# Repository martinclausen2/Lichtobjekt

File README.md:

# Lichtobjekt

The "Lichtobjekt" projects allows to create portable lighting appliances.

## Features

- Two independent LED driver channels
  - Flicker free brightness control through current adjustment
- Integrated Li Ion battery charger
- Status LED to indicate power on, channel, standby, and charging status
- Brightness measurement to adjust brightness at power on
- IR remote control (receiver and sender)
  -	Option to network devices
- Single rotational encoder and switch needed to control
- Embedded terminal to control settings, clock, and alarms

## Technical Features
- ARM Cortex M3 based STM32L151 microcontroller
  - EEPROM for permanent storage of settings
- RC5 based communication (sender and receiver)
- Two TPS61165DBVT step-up LED driver with PWM adjustment of LED driving current up to 350mA
- High dynamic brightness measurement with low cost phototransistor SFH320
- Low power design
  - Shutdown for IR receiver and voltage measurement
  - MCU power down and frequency adjustment
  - Low power logic voltage regulation with MCP1703
- Integrated Li Ion charger based on BQ2057WSN
  - Battery temperature monitoring
  - Charging status
  - 2S cell configuration
- PCB prepared (not used in current software) for 
  - Acceleration sensor MMA8452
  - Pin headers for extension with additional I2C devices, LCD, or LED drivers
  - RTC RV3029-C2 - currently the MCU's internal RTC is utilized 
  - EEPROM from 24CXXX series with I2C connection - currently the MCU's internal EEPROM is utilized, the EEPROM can be populated if other STM32 MCU are to be used which do not contain a EEPROM

# Design description

## Hardware

### MCU
The STM32L1 series features for this application relevant features like a large number of timers, specific low power modes, and an embedded EEPROM.

The MCU can be programmed and debugged via SWD accessable through a custom pin header, that also exposes the serial port.

### LED Driver
To drive a sufficient number of LEDs for edge illumination without efficiency reducing current balancing resistors, a LED driver with a step-up topology was selected. A two cell battery increases the efficiency of the step-up LED driver.

### RC5 receiver and sender

A IR emitting diode is driven by a small MOSFET from the PWM output of a timer in the MCU to send RC5 commands.

To receive RC5 commands the output of the IR receiver is sampled at a rate of about 4.5kHz by the MCU. The power supply of the IR receiver is cut in standby mode to prevent the battery to be drained prematurely.

### Brightness Sensor

The ambient brightness is sensed via an in expensive a broadly available phototransistor SFA 320. To enhance the dynamic range, the MCU can switch the bias current between two different levels.
The precision is fully sufficient to adjust the brightness of the power LEDs at power on and dim the status LED in standby.

### Battery Charger

The battery charger follows example application of the BQ2057 charging controller. The input voltage should be 9 V to avoid excessive power dissipation in the charging current regulating power transistor.
In newer hardware revision could switch off the charger during overvoltage conditions - However, the implementation in software is currently pending.
The status output is read by the MCU, that controls the status LED accordingly.
A temperature sensor is used to stop the charging if an overtemperature condition of the battery is detected.

## Software

TBA

## Known Limitations
- Very low power modes of MCU cannot be used, since to polarity of the encoder switch is not suitable.
- The MCU does not switch the battery charger off, if the input voltage would lead to a thermal overload of the charging transistor.
The batch of pcb made is missing the required hardware prerequisites. The latest version contains the required circuits, but has not been manufactured yet.
The batch is also missing the MOSFET to shutdown the battery temperature and external voltage measurement. Due to the high leakage current of the charging transistor, the battery is drained with about 400µA also during power down.
- The ioc file currently targets the STM32L151 which is not available anymore. The setup can easily be changed to the STM32L151A.

# User Manual

The user interface is rather simplistic.

Turning the encoder increases or decreases the brightness.
The integrated push button is used to select functionality and change between on and off.
Detailed settings can be adjusted via the serial terminal.

Coming from standby a short button press switches the light on. A long button press activates the networked mode, where other compatible lighting appliances receive commands to follow on, off, and brightness settings.

When the appliance in on the short button press selects between the two individual LED strings and a mode where the brightness is modulated between the two channels.

When the button is pressed, the status led previews a for a short time the next selected functionality.

Standby can be reached via a long button pressed from power on mode.

| LED Color 	| Condition | Status   | 
| :------------ | :------ | :------- |
| red			|         | standby  |
| white			|         | power on |
| blue flashing |         | charging |
| green flash	| while adjusting brightness | maximum brightness reached |
| red flash		| while adjusting brightness | minimum brightness reached |
| white flash	| pressing the button short | selected first LED channel  |
| red flash		| pressing the button short | selected second LED channel |
| pink flash	| pressing the button short | selected mood light mode	      |
| blue flash	| pressing the button long to power off | duration of flash corresponds to the charging status of the battery |
| green flash	| pressing the button very long | cancel button pressed |

The white flash is actually not visible, since the LED is already shining white.

# Configuration Manual

The serial port uses the following parameter 115200 Baud rate, data site 8, parity none, stop bits 1

The commands can be listed by sending the command 'help'.

## Available Commands

### Set Brightness

	bright [type] <-c channel_no> <-b brightness_value>

set brightness values

| Type | Decription |
| :--- | :--------- |
| 0 | Brightness last used before lights were switched off. |
| 1 | Minimum brightness when switched on |
| 2 | Maximum brightness any time |
| 3 | Maximum brightness when an alarm is triggered |
| 4 | PWM offset for brightness |
| 5 | Current brightness |

### Get External Brightness

	getextbright

Get the external brightness from the phototransistor

### Infrared Remote Control

	remote <-a address> <-rm receiver mode> <-sm sender mode> <-sa send address> <-sd send data>

set infrared remote parameters

| Mode | Decription |
| :--- | :--------- |
| 0 | Off |
| 1 | Alarm |
| 2 | Condional |
| 3 | All |

### Set Date and Time

	time [hour] [minute] [second]

set time of RTC

	date [2 digit year] [month] [day] [w] with w weekday

set date of RTC

	timestamp

get date and time from RTC

### Alarm

	alarmschedule [alarm no] <-w weekday> <-h hour> <-m minute>

set alarm schedule

	alarmsetting <-f time to fade-in light>

set alarm parameters
	
	alarm <-a 1 | 0> <-s alarm skip count>

trigger, reset, set alarm skip count

### Power and Battery

	power <-l 1 | 0>\r\n<-ub battery voltage> <-mub minimum battery voltage>\r\n<-up external power voltage> <-mup minimum external power voltage difference>

switch light, set min external power and battery voltage and calibration

Voltages are given in mV.

### Reset Settings

	reset

reset settings to factory defaults

### Status LED

	statusled [flash count]

flash status led

### Mood light

	fadelight <-f 1 | 0> time - <-t time> <-b brightness> <-mb maximum brightness>

switch and parameterize on mood light

### Version

	version

show STM32 software version

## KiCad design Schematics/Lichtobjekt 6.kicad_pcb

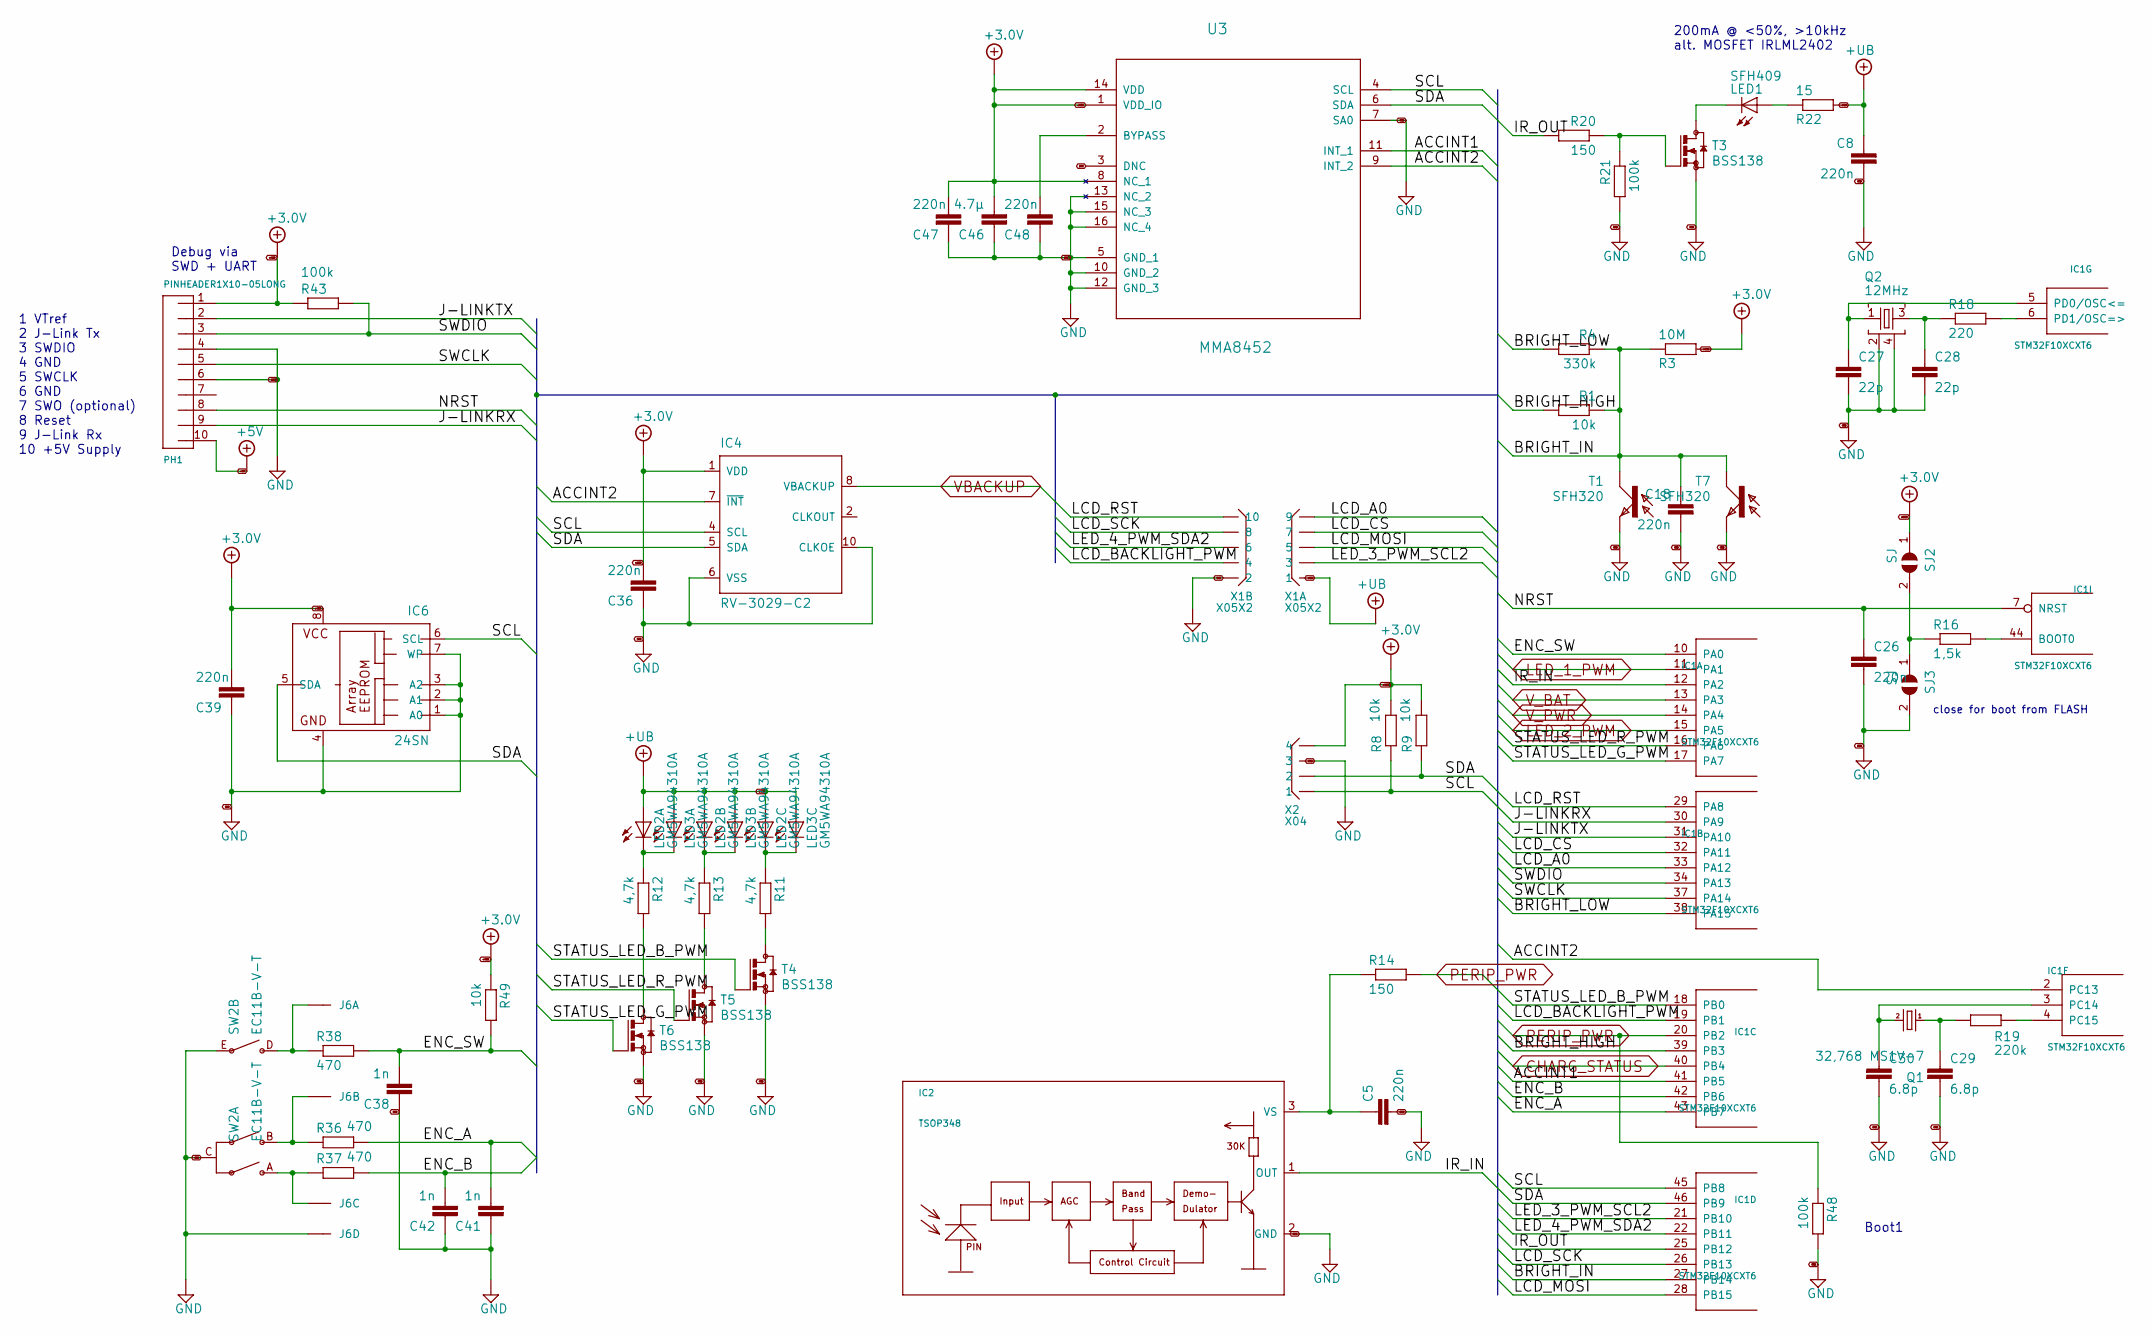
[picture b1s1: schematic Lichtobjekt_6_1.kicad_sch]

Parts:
C5, C8, C18, C26, C36, C39, C47, C48: 220n; C0603
C27, C28: 22p; C0603
C29, C30: 6.8p; C0603
C38, C41, C42: 1n; C0603
C46: 4.7µ; C0805
IC1: STM32F10XCXT6; TQFP48
IC2: TSOP348
IC4: RV-3029-C2; SON-10
IC6: 24SN; SO-08
J6: 22-?-0427-2041; 6410-04
LED1: SFH409; LED3MM
LED2, LED3: GM5WA94310A
PH1: PINHEADER1X10-05LONG; PINHEADER_005-1-10
Q1: 32,768 MS1V-7; MS1V-T1K
Q2: 12MHz; 3.4X2.7-4-PAD
R1, R8, R9, R49: 10k; R0805
R3: 10M; R0805
R4: 330k; R0805
R11, R12, R13: 4,7k; R0805
R14, R20: 150; R0805
R16: 1,5k; R0805
R18: 220; R0805
R19: 220k; R0805
R21, R43, R48: 100k; R0805
R22: 15; R1206
R36, R37, R38: 470; R0805
SJ2, SJ3: SJ
SW2: EC11B-V-T; EC11B-V
T1, T7: SFH320; LED_PLCC-2
T3, T4, T5, T6: BSS138; SOT23
U3: MMA8452; LGA16R50P3X5_300X300X100
X1: X05X2; X10N-IDC
X2: X04; X04N-SIL

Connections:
+5V: PH1.10; also elsewhere on the board
+UB: C8.1, LED2.1 (A), LED2.2 (A), LED2.3 (A), LED3.1 (A), LED3.2 (A), LED3.3 (A), R22.2, X1.1; also elsewhere on the board
+UB3: C36.1, C39.1, C46.2, C47.1, IC4.1 (VDD), IC6.8 (VCC), PH1.1, R3.2, R8.2, R9.2, R43.1, R49.1, SJ2.1, U3.1 (VDD_IO), U3.8 (NC_1), U3.14 (VDD), X2.4; also elsewhere on the board
/Lichtobjekt 6_1/ACCINT1: IC1.41 (PB5), U3.11 (INT_1)
/Lichtobjekt 6_1/ACCINT2: IC1.2 (PC13), IC4.7 (~INT), U3.9 (INT_2)
/Lichtobjekt 6_1/BRIGHT_HIGH: IC1.39 (PB3), R1.2
/Lichtobjekt 6_1/BRIGHT_IN: C18.1, IC1.27 (PB14), R1.1, R3.1, R4.1, T1.1 (C), T7.1 (C)
/Lichtobjekt 6_1/BRIGHT_LOW: IC1.38 (PA15), R4.2
/Lichtobjekt 6_1/ENC_A: C41.2, IC1.43 (PB7), R36.2
/Lichtobjekt 6_1/ENC_B: C42.2, IC1.42 (PB6), R37.2
/Lichtobjekt 6_1/ENC_SW: C38.2, IC1.10 (PA0), R38.2, R49.2
/Lichtobjekt 6_1/IR_IN: IC1.12 (PA2), IC2.1 (OUT)
/Lichtobjekt 6_1/IR_OUT: IC1.25 (PB12), R20.2
/Lichtobjekt 6_1/J-LINKRX: IC1.30 (PA9), PH1.9
/Lichtobjekt 6_1/J-LINKTX: IC1.31 (PA10), PH1.2
/Lichtobjekt 6_1/LCD_A0: IC1.33 (PA12), X1.9
/Lichtobjekt 6_1/LCD_BACKLIGHT_PWM: IC1.19 (PB1), X1.4
/Lichtobjekt 6_1/LCD_CS: IC1.32 (PA11), X1.7
/Lichtobjekt 6_1/LCD_MOSI: IC1.28 (PB15), X1.5
/Lichtobjekt 6_1/LCD_RST: IC1.29 (PA8), X1.10
/Lichtobjekt 6_1/LCD_SCK: IC1.26 (PB13), X1.8
/Lichtobjekt 6_1/LED_3_PWM_SCL2: IC1.21 (PB10), X1.3
/Lichtobjekt 6_1/LED_4_PWM_SDA2: IC1.22 (PB11), X1.6
/Lichtobjekt 6_1/NRST: C26.1, IC1.7 (NRST), PH1.8
/Lichtobjekt 6_1/SCL: IC1.45 (PB8), IC4.4 (SCL), IC6.6 (SCL), R8.1, U3.4 (SCL), X2.1
/Lichtobjekt 6_1/SDA: IC1.46 (PB9), IC4.5 (SDA), IC6.5 (SDA), R9.1, U3.6 (SDA), X2.2
/Lichtobjekt 6_1/STATUS_LED_B_PWM: IC1.18 (PB0), T4.1 (G)
/Lichtobjekt 6_1/STATUS_LED_G_PWM: IC1.17 (PA7), T6.1 (G)
/Lichtobjekt 6_1/STATUS_LED_R_PWM: IC1.16 (PA6), T5.1 (G)
/Lichtobjekt 6_1/SWCLK: IC1.37 (PA14), PH1.5
/Lichtobjekt 6_1/SWDIO: IC1.34 (PA13), PH1.3, R43.2
CHARG_STATUS: IC1.40 (PB4); also elsewhere on the board
DNC: U3.3 (DNC)
GND: C5.2, C8.2, C18.2, C26.2, C27.2, C28.2, C29.2, C30.2, C36.2, C38.1, C39.2, C41.1, C42.1, C46.1, C47.2, C48.2, IC2.2 (GND), IC4.6 (VSS), IC4.10 (CLKOE), IC6.1 (A0), IC6.2 (A1), IC6.3 (A2), IC6.4 (GND), IC6.7 (WP), J6.4, PH1.4, PH1.6, Q2.2, Q2.4, R21.2, R48.2, SJ3.2, SW2.C, SW2.E, T1.2 (E), T3.2 (S), T4.2 (S), T5.2 (S), T6.2 (S), T7.2 (E), U3.5 (GND_1), U3.7 (SA0), U3.10 (GND_2), U3.12 (GND_3), U3.13 (NC_2), U3.15 (NC_3), U3.16 (NC_4), X1.2, X2.3; also elsewhere on the board
LED_1_PWM: IC1.11 (PA1); also elsewhere on the board
LED_2_PWM: IC1.15 (PA5); also elsewhere on the board
unnamed: C5.1, IC2.3 (VS), R14.1
unnamed: C27.1, IC1.5 (PD0/OSC<=), Q2.1
unnamed: C28.1, Q2.3, R18.1
unnamed: C29.1, Q1.1, R19.1
unnamed: C30.1, IC1.3 (PC14), Q1.4 (2)
unnamed: C48.1, U3.2 (BYPASS)
unnamed: IC1.4 (PC15), R19.2
unnamed: IC1.6 (PD1/OSC=>), R18.2
unnamed: IC1.44 (BOOT0), R16.2
unnamed: J6.1, R38.1, SW2.D
unnamed: J6.2, R36.1, SW2.B
unnamed: J6.3, R37.1, SW2.A
unnamed: LED1.A, R22.1
unnamed: LED1.K (C), T3.3 (D)
unnamed: LED2.4 (C), LED3.4 (C), R13.1
unnamed: LED2.5 (C), LED3.5 (C), R12.1
unnamed: LED2.6 (C), LED3.6 (C), R11.1
unnamed: R11.2, T4.3 (D)
unnamed: R12.2, T6.3 (D)
unnamed: R13.2, T5.3 (D)
unnamed: R16.1, SJ2.2, SJ3.1
unnamed: R20.1, R21.1, T3.1 (G)
PERIP_PWR: IC1.20 (PB2), R14.2, R48.1; also elsewhere on the board
VBACKUP: IC4.8 (VBACKUP); also elsewhere on the board
V_BAT: IC1.13 (PA3); also elsewhere on the board

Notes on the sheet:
Debug via SWD + UART
200mA @ <50%, >10kHz alt. MOSFET IRLML2402
close for boot from FLASH
Boot1
1 VTref 2 J-Link Tx 3 SWDIO 4 GND 5 SWCLK 6 GND 7 SWO (optional) 8 Reset 9 J-Link Rx 10 +5V Supply

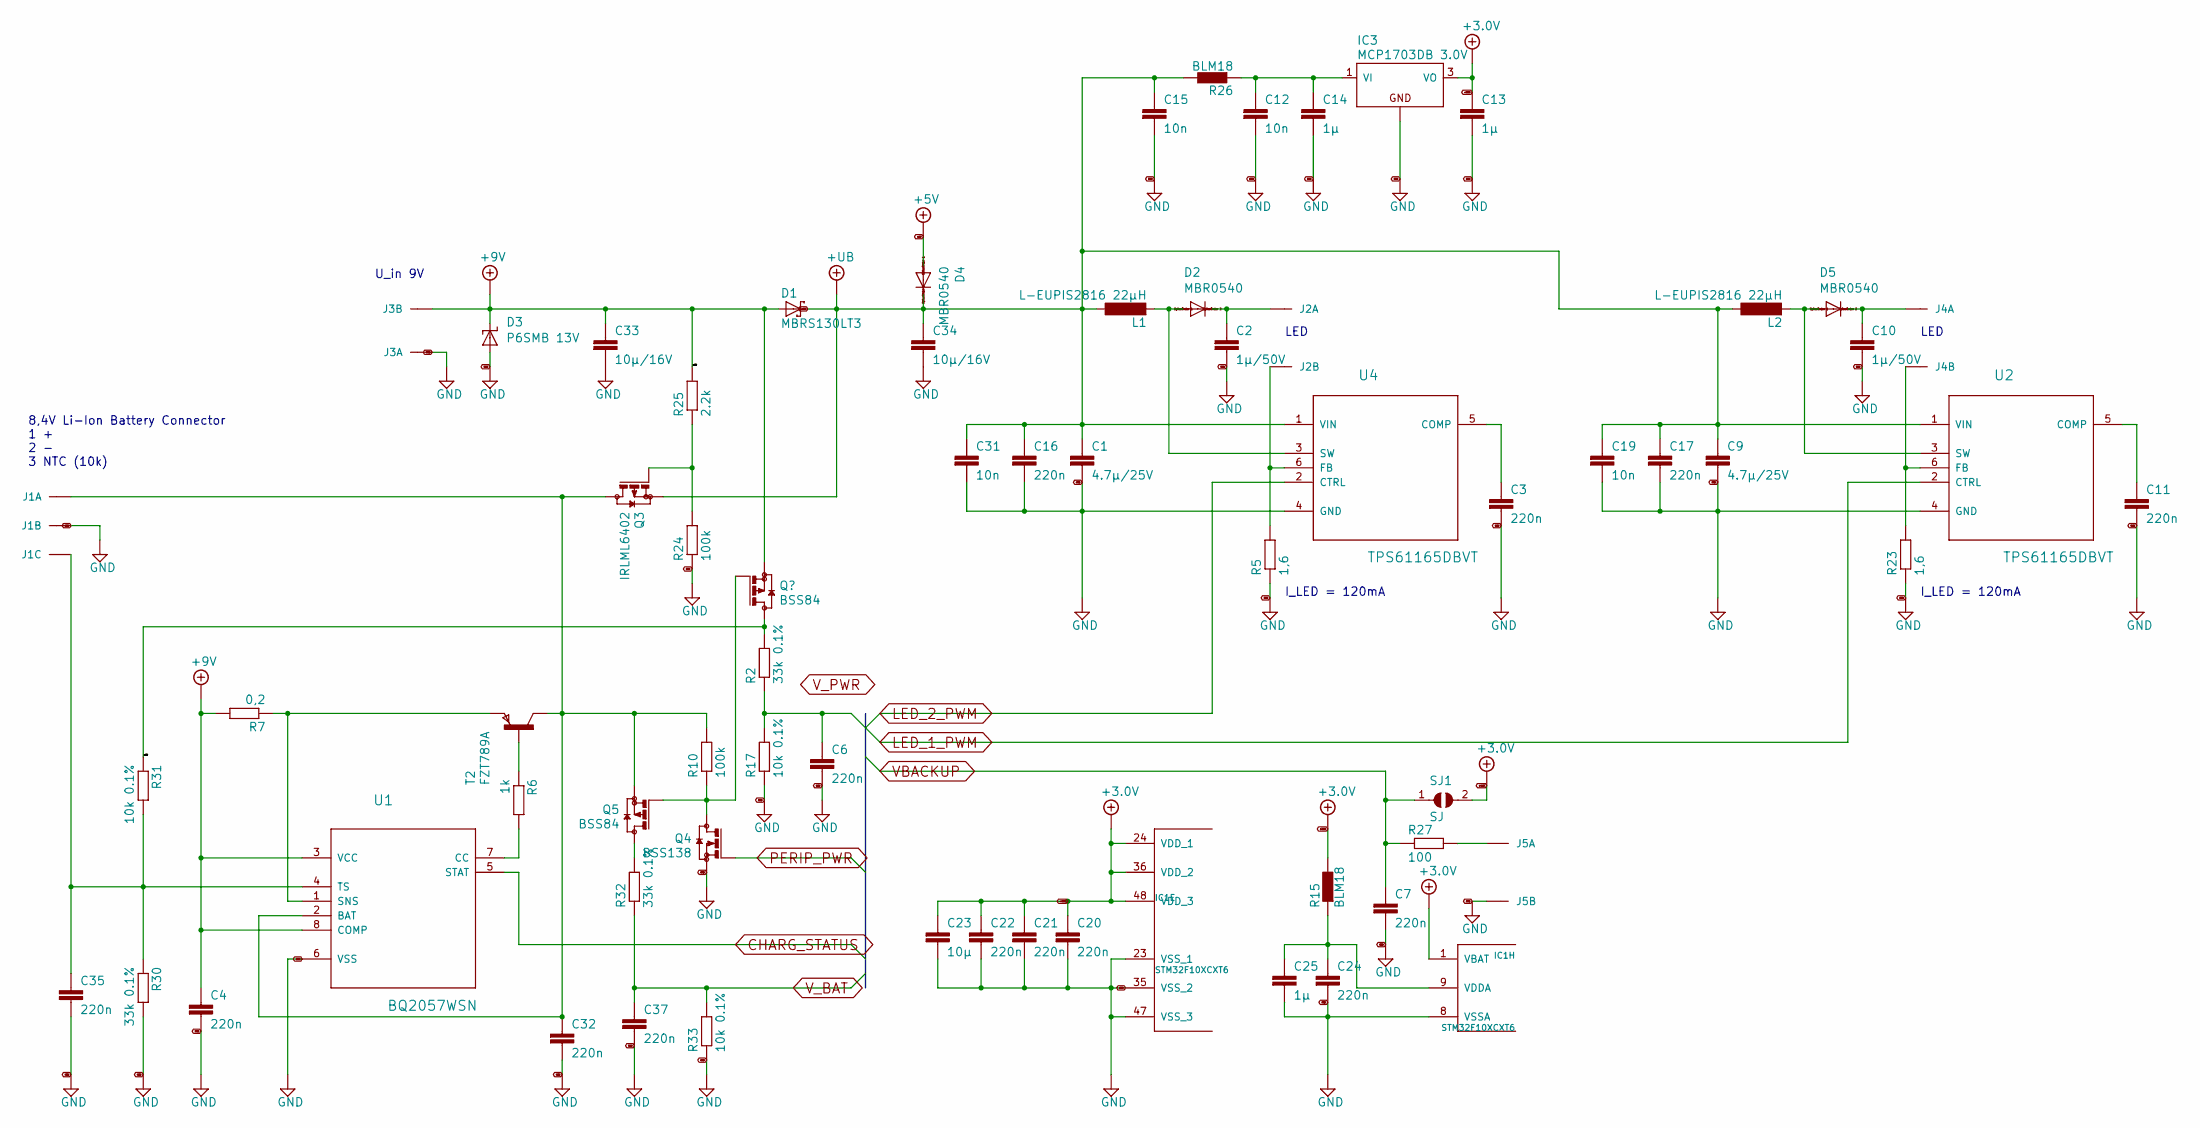
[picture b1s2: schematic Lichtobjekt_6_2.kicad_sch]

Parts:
C1, C9: 4.7µ/25V; C0805
C2, C10: 1µ/50V; C0805
C3, C4, C6, C7, C11, C16, C17, C20, C21, C22, C24, C32, C35, C37: 220n; C0603
C12, C15, C19, C31: 10n; C0603
C13, C14, C25: 1µ; C0805
C23: 10µ; C0805
C33, C34: 10µ/16V; C1210
D1: MBRS130LT3; SMB
D2, D4, D5: MBR0540; SOD123
D3: P6SMB 13V; SMBJ
IC1: STM32F10XCXT6; TQFP48
IC3: MCP1703DB 3.0V; SOT223
J1: 22-27-2031-03; 6410-03
J2, J3, J4, J5: 22-?-0227-2021; 6410-02
L1, L2: L-EUPIS2816 22µH; PIS28XX
Q3: IRLML6402; SOT23
Q4: BSS138; SOT23
Q5: BSS84; SOT23
R2, R30, R32: 33k 0.1%; R0805
R5, R23: 1,6; R1206
R6: 1k; R0805
R7: 0,2; R1206
R10, R24: 100k; R0805
R15, R26: BLM18; R0805
R17, R31, R33: 10k 0.1%; R0805
R25: 2.2k; R0805
R27: 100; R0805
SJ1: SJ
T2: FZT789A; SOT223
U1: BQ2057WSN; SOIC127P600X175-8N
U2, U4: TPS61165DBVT; SOT95P280X145-6N

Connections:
+5V: D4.A; also elsewhere on the board
+9V: C4.1, C33.1, D1.A, D3.C, J3.2, R2.2, R7.2, R25.2, R31.1, U1.3 (VCC), U1.8 (COMP)
+UB: C1.1, C9.1, C15.1, C16.1, C17.1, C19.1, C31.1, C34.1, D1.C, D4.C, L1.2 (1), L2.2 (1), Q3.2 (S), R26.2, U2.1 (VIN), U4.1 (VIN); also elsewhere on the board
+UB3: C13.1, C20.1, C21.1, C22.1, C23.1, IC1.1 (VBAT), IC1.24 (VDD_1), IC1.36 (VDD_2), IC1.48 (VDD_3), IC3.3 (VO), R15.2, SJ1.2; also elsewhere on the board
CHARG_STATUS: U1.5 (STAT); also elsewhere on the board
GND: C1.2, C2.2, C3.2, C4.2, C6.2, C7.2, C9.2, C10.2, C11.2, C12.2, C13.2, C14.2, C15.2, C16.2, C17.2, C19.2, C20.2, C21.2, C22.2, C23.2, C24.2, C25.2, C31.2, C32.2, C33.2, C34.2, C35.2, C37.2, D3.A, IC1.8 (VSSA), IC1.23 (VSS_1), IC1.35 (VSS_2), IC1.47 (VSS_3), IC3.2 (GND), IC3.4 (GND), J1.2, J3.1, J5.2, Q4.2 (S), R5.1, R17.1, R23.1, R24.1, R30.2, R33.1, U1.6 (VSS), U2.4 (GND), U4.4 (GND); also elsewhere on the board
LED_1_PWM: U2.2 (CTRL); also elsewhere on the board
LED_2_PWM: U4.2 (CTRL); also elsewhere on the board
unnamed: C2.1, D2.C, J2.1
unnamed: C3.1, U4.5 (COMP)
unnamed: C10.1, D5.C, J4.1
unnamed: C11.1, U2.5 (COMP)
unnamed: C12.1, C14.1, IC3.1 (VI), R26.1
unnamed: C24.1, C25.1, IC1.9 (VDDA), R15.1
unnamed: C32.1, J1.1, Q3.3 (D), Q5.2 (S), R10.2, T2.2 (C), T2.4 (C), U1.2 (BAT)
unnamed: C35.1, J1.3, R30.1, R31.2, U1.4 (TS)
unnamed: D2.A, L1.1 (2), U4.3 (SW)
unnamed: D5.A, L2.1 (2), U2.3 (SW)
unnamed: J2.2, R5.2, U4.6 (FB)
unnamed: J4.2, R23.2, U2.6 (FB)
unnamed: J5.1, R27.2
unnamed: Q3.1 (G), R24.2, R25.1
unnamed: Q4.3 (D), Q5.1 (G), R10.1
unnamed: Q5.3 (D), R32.2
unnamed: R6.1, T2.1 (B)
unnamed: R6.2, U1.7 (CC)
unnamed: R7.1, T2.3 (E), U1.1 (SNS)
PERIP_PWR: Q4.1 (G); also elsewhere on the board
VBACKUP: C7.1, R27.1, SJ1.1; also elsewhere on the board
V_BAT: C37.1, R32.1, R33.2; also elsewhere on the board

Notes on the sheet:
I_LED = 120mA
LED
U_in 9V
8,4V Li-Ion Battery Connector 1 + 2 - 3 NTC (10k)

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
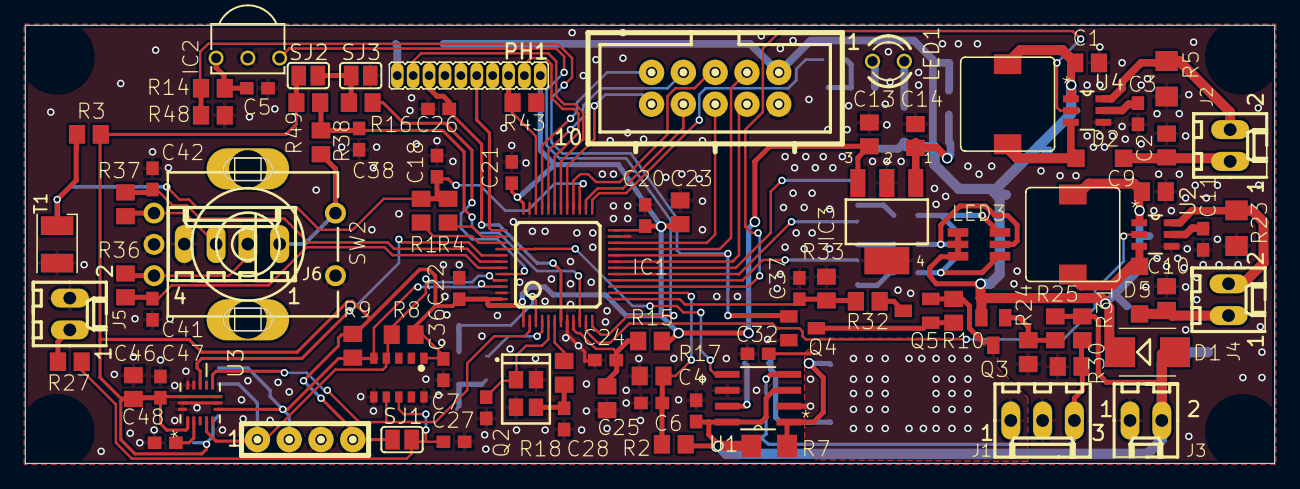
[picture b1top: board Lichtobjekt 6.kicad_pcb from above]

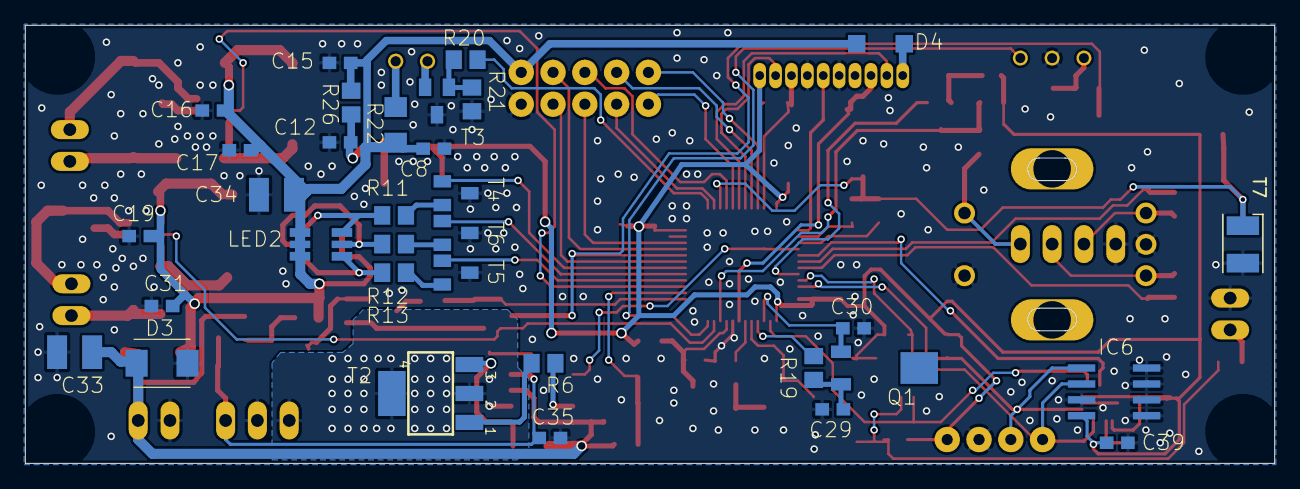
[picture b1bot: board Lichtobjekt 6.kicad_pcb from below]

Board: 2 copper layers, 99.8 x 35.0 mm, 125 parts (33 on the bottom side), 81 nets.

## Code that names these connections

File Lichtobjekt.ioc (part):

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Mcu.Name=STM32L151C(6-8-B)Tx
Mcu.Package=LQFP48
Mcu.UserName=STM32L151CBTx
PA0-WKUP1.GPIOParameters=GPIO_PuPd,GPIO_Label,GPIO_ModeDefaultEXTI
PA0-WKUP1.GPIO_Label=ENC_SW
PA0-WKUP1.GPIO_ModeDefaultEXTI=GPIO_MODE_IT_FALLING
PA0-WKUP1.GPIO_PuPd=GPIO_PULLUP
PA0-WKUP1.Signal=GPXTI0
PA1.GPIOParameters=GPIO_Speed,GPIO_PuPd,GPIO_Label
PA1.GPIO_Label=LED_2_PWM
PA1.GPIO_PuPd=GPIO_PULLDOWN
PA1.GPIO_Speed=GPIO_SPEED_FREQ_MEDIUM
PA1.Signal=S_TIM2_CH2
PA10.GPIOParameters=GPIO_PuPd,GPIO_Label
PA10.GPIO_Label=J_LinkTX
PA10.GPIO_PuPd=GPIO_PULLDOWN
PA10.Mode=Asynchronous
PA10.Signal=USART1_RX
PA11.Signal=GPIO_Analog
PA12.Signal=GPIO_Analog
PA13.GPIOParameters=GPIO_Label
PA13.GPIO_Label=SWDIO
PA13.Mode=Serial_Wire
PA13.Signal=SYS_JTMS-SWDIO
PA14.GPIOParameters=GPIO_Label
PA14.GPIO_Label=SWCLK
PA14.Mode=Serial_Wire
PA14.Signal=SYS_JTCK-SWCLK
PA15.GPIOParameters=PinState,GPIO_Label
PA15.GPIO_Label=BRIGHT_LOW
PA15.PinState=GPIO_PIN_SET
PA15.Signal=GPIO_Output
PA2.GPIOParameters=GPIO_Label
PA2.GPIO_Label=IR_IN
PA2.Signal=GPIO_Input
PA3.GPIOParameters=GPIO_Label
PA3.GPIO_Label=U Bat
PA3.Mode=IN3
PA3.Signal=ADC_IN3
PA4.GPIOParameters=GPIO_Label
PA4.GPIO_Label=U Pwr
PA4.Mode=IN4
PA4.Signal=ADC_IN4
PA5.GPIOParameters=GPIO_Speed,GPIO_PuPd,GPIO_Label
PA5.GPIO_Label=LED_1_PWM
PA5.GPIO_PuPd=GPIO_PULLDOWN
PA5.GPIO_Speed=GPIO_SPEED_FREQ_MEDIUM
PA5.Signal=S_TIM2_CH1_ETR
PA6.GPIOParameters=GPIO_PuPd,GPIO_Label
PA6.GPIO_Label=STATUS_LED_R_PWM
PA6.GPIO_PuPd=GPIO_PULLDOWN
PA6.Signal=S_TIM3_CH1
PA7.GPIOParameters=GPIO_PuPd,GPIO_Label
PA7.GPIO_Label=STATUS_LED_G_PWM
PA7.GPIO_PuPd=GPIO_PULLDOWN
PA7.Signal=S_TIM3_CH2
PA8.Signal=GPIO_Analog
PA9.GPIOParameters=GPIO_Label
PA9.GPIO_Label=J-LinkRX
PA9.Mode=Asynchronous
PA9.Signal=USART1_TX
PB0.GPIOParameters=GPIO_PuPd,GPIO_Label
PB0.GPIO_Label=STATUS_LED_B_PWM
PB0.GPIO_PuPd=GPIO_PULLDOWN
PB0.Signal=S_TIM3_CH3
PB1.Signal=GPIO_Analog
PB10.Signal=GPIO_Analog
PB11.Signal=GPIO_Analog
PB12.GPIOParameters=GPIO_Speed,GPIO_PuPd,GPIO_Label
PB12.GPIO_Label=IR_OUT
PB12.GPIO_PuPd=GPIO_PULLDOWN
PB12.GPIO_Speed=GPIO_SPEED_FREQ_HIGH
PB12.Signal=S_TIM10_CH1
PB13.Signal=GPIO_Analog
PB14.GPIOParameters=GPIO_Label
PB14.GPIO_Label=BRIGHT_IN
PB14.Mode=IN20
PB14.Signal=ADC_IN20
PB15.Signal=GPIO_Analog
PB2.GPIOParameters=PinState,GPIO_Label
PB2.GPIO_Label=PERIP_PWR
PB2.PinState=GPIO_PIN_SET
PB2.Signal=GPIO_Output
PB3.GPIOParameters=PinState,GPIO_Label
PB3.GPIO_Label=BRIGHT_HIGH
PB3.PinState=GPIO_PIN_SET
PB3.Signal=GPIO_Output
PB4.GPIOParameters=GPIO_PuPd,GPIO_Label
PB4.GPIO_Label=Charging_Status
PB4.GPIO_PuPd=GPIO_PULLDOWN
PB4.Signal=GPIO_Input
PB5.Signal=GPIO_Analog
PB6.GPIOParameters=GPIO_PuPd,GPIO_Label
PB6.GPIO_Label=ENC_B
PB6.GPIO_PuPd=GPIO_PULLUP
PB6.Signal=S_TIM4_CH1
PB7.GPIOParameters=GPIO_PuPd,GPIO_Label
PB7.GPIO_Label=ENC_A
PB7.GPIO_PuPd=GPIO_PULLUP
PB7.Signal=S_TIM4_CH2
PB8.Signal=GPIO_Analog
PB9.Signal=GPIO_Analog
PC13-WKUP2.Signal=GPIO_Analog
PC14-OSC32_IN.Mode=LSE-External-Oscillator
PC14-OSC32_IN.Signal=RCC_OSC32_IN
PC15-OSC32_OUT.Mode=LSE-External-Oscillator
PC15-OSC32_OUT.Signal=RCC_OSC32_OUT
RCC.HSE_VALUE=24000000
RCC.SYSCLKFreq_VALUE=16000000
RCC.SYSCLKSource=RCC_SYSCLKSOURCE_HSI
board=Lichtobjekt

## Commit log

2018-05-06 added schematics
2021-03-28 added updated schematics and pin out file
2021-06-05 version of PCB produced first version to show basic functionality incl. remote and serial monitor output
2021-06-05 adjust configuration tim3 fix status led
2021-06-05 fix warnings change MCU to model with more memory C6 => CB suffix
2022-12-28 added missing init for sender mode added persistence for settings and last brightness measured via sensor code compiles is untested with respect to persistence and brightness measurement. added missi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
2022-12-28 clean up header enable brightness measurement
2023-05-30 updated HAL version added terminal
2023-06-08 updated with latest code from RGBW-Lampe
2023-06-08 removed unused pin configuration adjusted MSI frequency and PWM range to maintain min. 5kHz PWM frequency with MSI osc disabled RC5 and CRC, both currently broken started to work on voltage measureme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
2023-06-10 minor code cleanup fix missing array size added DMA for ADC run core at 8 to keep up with interrupts during RC5 encoding and better PWM resolution replace wake up pin with ext interrupted due to wron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
    known issues: RC5 encoder not working, early weak up form low power standby, missing low power stand by for battery operation
2023-06-10 added battery deep power down added measures to minimize power consumption in stop mode
2023-06-11 added P-MOSFET to switch voltage and temp measurements to avoid battery draining due to leak current via charging pnp transistor and control charging of battery
2023-06-11 dynamically switch to 16 MHz during RC5 encoding, at 8 MHz the timing was incorrect
2023-07-16 fix crc by replacing old sysmem.c fix comments and terminal output texts
2023-07-16 added address to remote command in terminal
2023-07-16 cleanup logging
2023-10-07 apply changes and fixes to skip alarm and terminal
2023-10-07 fix fadelight and alarmskipcounter
2023-10-10 fix statusled fix error handling, remove dely in UART code for terminal add version command
2023-10-11 fix remote control from other lamp switch off time of standby led in battery mode indicates battery voltage
2023-10-11 fix battery indicator
2023-10-22 fix excessive end alarm command sent
2023-11-01 fix alarm end when command send via terminal
2023-11-05 minor fix in terminal
2023-12-23 added README.md minor fix update CubeMX version
2023-12-23 extended README.md
2023-12-23 enhanced README.md
2023-12-25 fixed encoder
2024-01-07 fix alarm start and end send via RC5
2024-01-09 remove dead code and fix brightness settings
2024-01-24 fix fadelight adjust encoder acceleration
2024-04-28 update CUBE MX version fix RC5 sender: duty cycle and toggle bit
